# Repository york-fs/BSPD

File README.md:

# Brake System Plausibility Device

Uses non-programmable logic to implement the Brake System Plausibility Device required by FSUK rules. The BSPD opens the low-voltage shutdown circuit in the event of current being delivered to the motor while hard braking occurs.

## Features
- TODO

## PCB Notes
- Designed in KiCad 9.0

## Cloning

A recursive clone must be used to download the `kicad-library` repository:

    git clone --recursive https://github.com/york-fs/bspd.git

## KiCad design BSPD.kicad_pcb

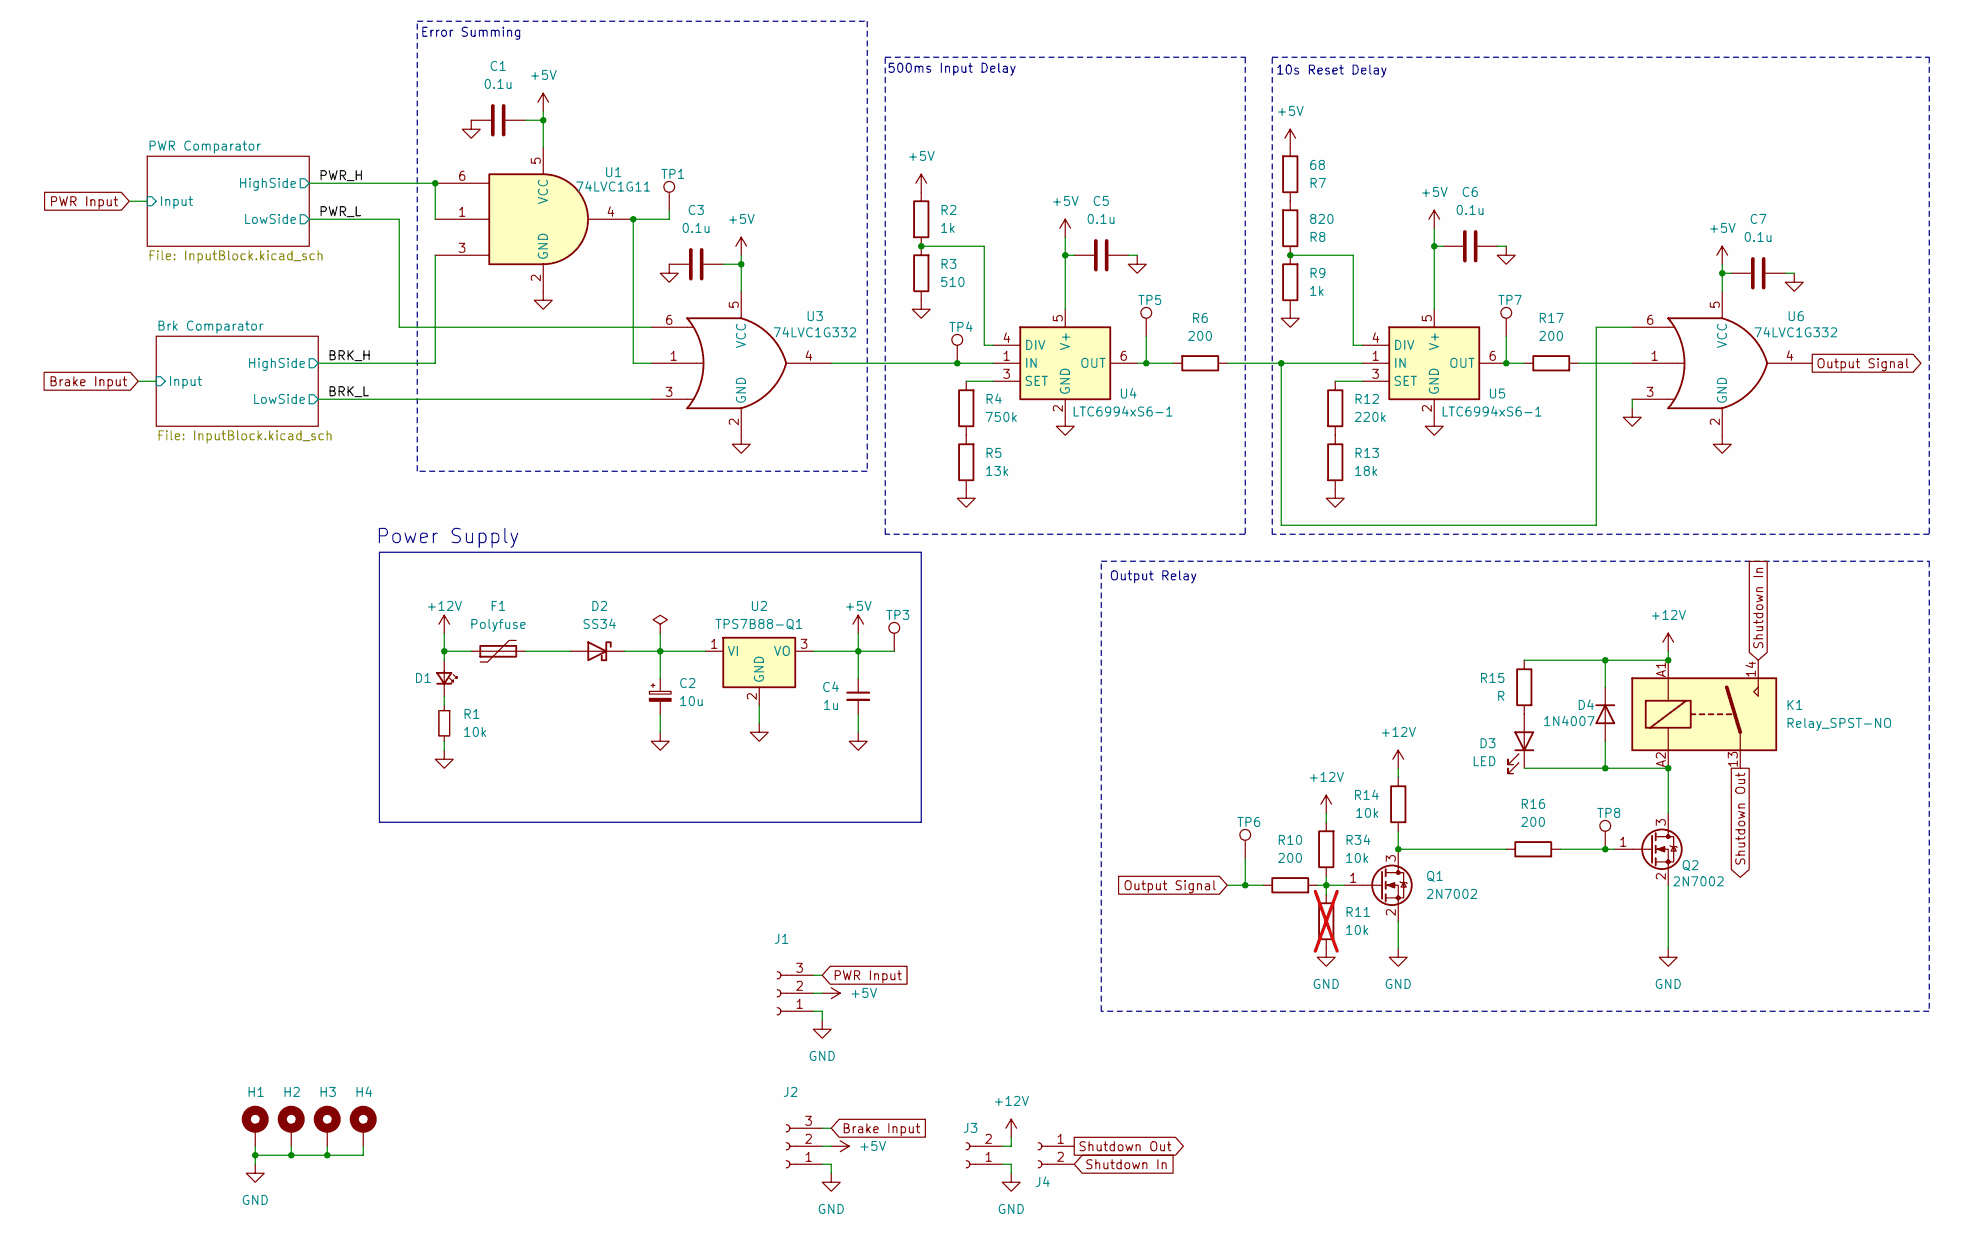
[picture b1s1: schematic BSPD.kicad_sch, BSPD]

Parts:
C1, C3, C5, C6, C7: 0.1u; C_0603_1608Metric
C2: 10u; CP_Elec_6.3x5.4
C4: 1u; C_0603_1608Metric
D1: LED_Small; LED_0603_1608Metric
D2: SS34; D_SMA
D3: LED; LED_0603_1608Metric
D4: 1N4007; D_SOD-123F
F1: Polyfuse; R_0805_2012Metric
H1, H2, H3, H4: MountingHole_Pad; MountingHole_3.2mm_M3_Pad_Via
J1, J2: Conn_01x03_Socket; MolexMicrofitPlus1x3
J3, J4: Conn_01x02_Socket; MolexMicrofitPlus1x2
K1: Relay_SPST-NO; Relay_SPST_Omron_G2RL-1A
Q1, Q2: 2N7002; SOT-23
R1, R14, R34: 10k; R_0603_1608Metric
R2, R9: 1k; R_0603_1608Metric
R3: 510; R_0603_1608Metric
R4: 750k; R_0603_1608Metric
R5: 13k; R_0603_1608Metric
R6, R10, R16, R17: 200; R_0603_1608Metric
R7: 68; R_0603_1608Metric
R8: 820; R_0603_1608Metric
R11: 10k; R_0603_1608Metric; not fitted
R12: 220k; R_0603_1608Metric
R13: 18k; R_0603_1608Metric
R15: R; R_0603_1608Metric
TP1, TP3, TP4, TP5, TP6, TP7, TP8: TestPoint; TestPoint_Keystone_5000-5004_Miniature
U1: 74LVC1G11; SOT-23-6
U2: TPS7B88-Q1; TO-252-2
U3, U6: 74LVC1G332; SOT-23-6
U4, U5: LTC6994xS6-1; TSOT-23-6

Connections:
+5V: C1.1, C3.1, C4.1, C5.2, C6.1, C7.1, J1.2, J2.2, R2.1, R7.2, TP3.1, U1.5 (VCC), U2.3 (VO), U3.5 (VCC), U4.5 (V+), U5.5 (V+), U6.5 (VCC); also elsewhere on the board
+12V: D1.2 (A), D4.1 (K), F1.1, J3.2, K1.A1, R14.1, R15.1, R34.2
/BRK_H: U1.3; also elsewhere on the board
/BRK_L: U3.3; also elsewhere on the board
/PWR_H: U1.1, U1.6; also elsewhere on the board
/PWR_L: U3.6; also elsewhere on the board
Brake Input: J2.3; also elsewhere on the board
GND: C1.2, C2.2, C3.2, C4.2, C5.1, C6.2, C7.2, H1.1, H2.1, H3.1, H4.1, J1.1, J2.1, J3.1, Q1.2 (S), Q2.2 (S), R1.2, R3.1, R5.1, R9.1, R11.2, R13.2, U1.2 (GND), U2.2 (GND), U3.2 (GND), U4.2 (GND), U5.2 (GND), U6.2 (GND), U6.3; also elsewhere on the board
unnamed: D1.1 (K), R1.1
unnamed: D2.2 (A), F1.2
unnamed: C2.1, D2.1 (K), U2.1 (VI)
unnamed: D3.2 (A), R15.2
unnamed: D3.1 (K), D4.2 (A), K1.A2, Q2.3 (D)
unnamed: Q1.3 (D), R14.2, R16.1
unnamed: Q1.1 (G), R10.2, R11.1, R34.1
unnamed: Q2.1 (G), R16.2, TP8.1
unnamed: R4.1, R5.2
unnamed: R7.1, R8.2
unnamed: R12.2, R13.1
unnamed: R17.2, U6.1
unnamed: TP1.1, U1.4, U3.1
unnamed: R2.2, R3.2, U4.4 (DIV)
unnamed: TP4.1, U3.4, U4.1 (IN)
unnamed: R6.2, TP5.1, U4.6 (OUT)
unnamed: R4.2, U4.3 (SET)
unnamed: R8.1, R9.2, U5.4 (DIV)
unnamed: R6.1, U5.1 (IN), U6.6
unnamed: R17.1, TP7.1, U5.6 (OUT)
unnamed: R12.1, U5.3 (SET)
Output Signal: R10.1, TP6.1, U6.4
PWR Input: J1.3; also elsewhere on the board
Shutdown In: J4.2, K1.14
Shutdown Out: J4.1, K1.13

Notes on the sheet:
500ms Input Delay
Error Summing
Power Supply
10s Reset Delay
Output Relay

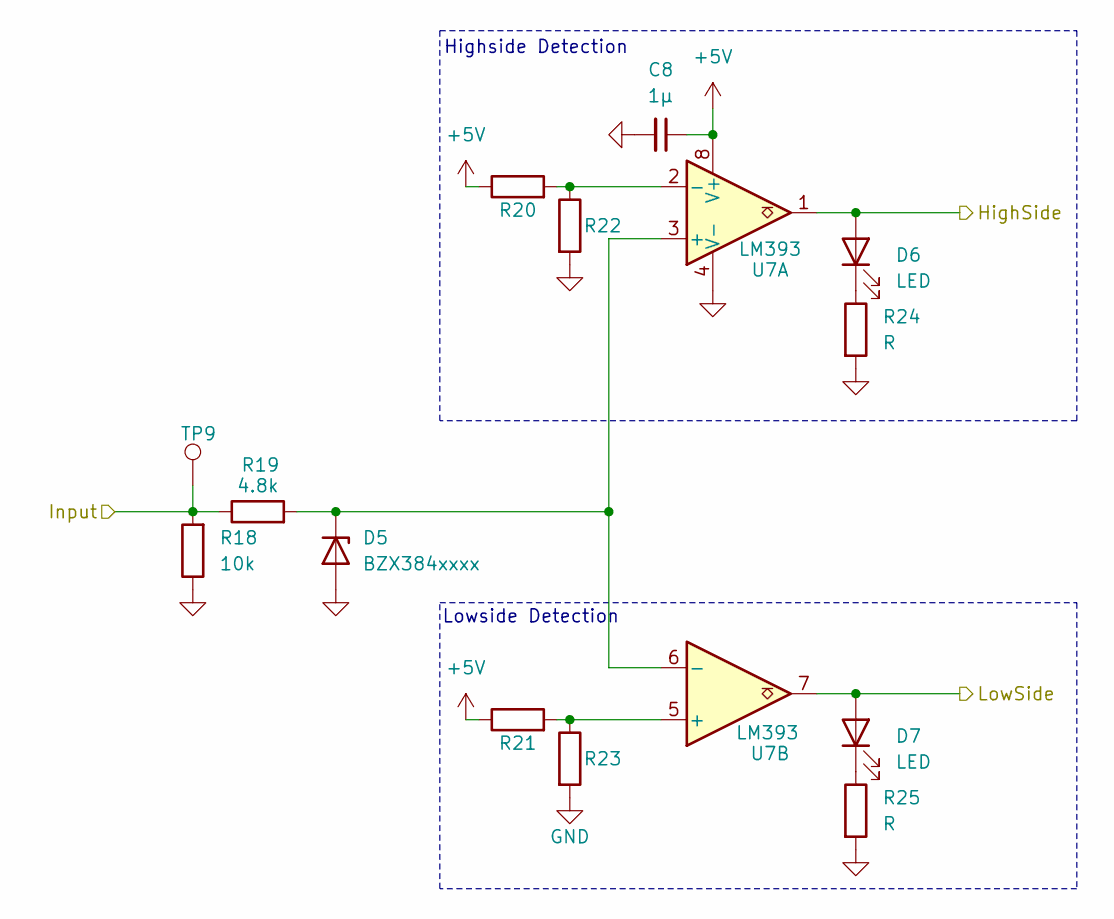
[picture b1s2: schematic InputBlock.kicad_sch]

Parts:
C8: 1µ; C_0603_1608Metric
D5: BZX384xxxx; D_SOD-323
D6, D7: LED; LED_0603_1608Metric
R18: 10k; R_0603_1608Metric
R19: 4.8k; R_0603_1608Metric
R20, R21: 39K; R_0603_1608Metric
R22, R23: 62k; R_0603_1608Metric
R24, R25: R; R_0603_1608Metric
TP9: TestPoint; TestPoint_Keystone_5000-5004_Miniature
U7: LM393; SOIC-8_3.9x4.9mm_P1.27mm

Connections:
+5V: C8.1, R20.1, R21.1, U7.8 (V+); also elsewhere on the board
/PWR_H: D6.2 (A), U7.1; also elsewhere on the board
/PWR_L: D7.2 (A), U7.7; also elsewhere on the board
GND: C8.2, D5.2 (A), R18.1, R22.2, R23.2, R24.2, R25.2, U7.4 (V-); also elsewhere on the board
unnamed: D5.1 (K), R19.2, U7.3 (+), U7.6 (-)
unnamed: D6.1 (K), R24.1
unnamed: D7.1 (K), R25.1
unnamed: R20.2, R22.1, U7.2 (-)
unnamed: R21.2, R23.1, U7.5 (+)
PWR Input: R18.2, R19.1, TP9.1; also elsewhere on the board

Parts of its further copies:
C9: 1µ; C_0603_1608Metric
D8: BZX384xxxx; D_SOD-323
D9, D10: LED; LED_0603_1608Metric
R26: 10k; R_0603_1608Metric
R27: 4.8k; R_0603_1608Metric
R28, R29: 39K; R_0603_1608Metric
R30, R31: 62k; R_0603_1608Metric
R32, R33: R; R_0603_1608Metric
TP10: TestPoint; TestPoint_Keystone_5000-5004_Miniature
U8: LM393; SOIC-8_3.9x4.9mm_P1.27mm

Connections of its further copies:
+5V: C9.1, R28.1, R29.1, U8.8 (V+); also elsewhere on the board
/BRK_H: D9.2 (A), U8.1; also elsewhere on the board
/BRK_L: D10.2 (A), U8.7; also elsewhere on the board
Brake Input: R26.2, R27.1, TP10.1; also elsewhere on the board
GND: C9.2, D8.2 (A), R26.1, R30.2, R31.2, R32.2, R33.2, U8.4 (V-); also elsewhere on the board
unnamed: D8.1 (K), R27.2, U8.3 (+), U8.6 (-)
unnamed: D9.1 (K), R32.1
unnamed: D10.1 (K), R33.1
unnamed: R28.2, R30.1, U8.2 (-)
unnamed: R29.2, R31.1, U8.5 (+)

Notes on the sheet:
Highside Detection
Lowside Detection

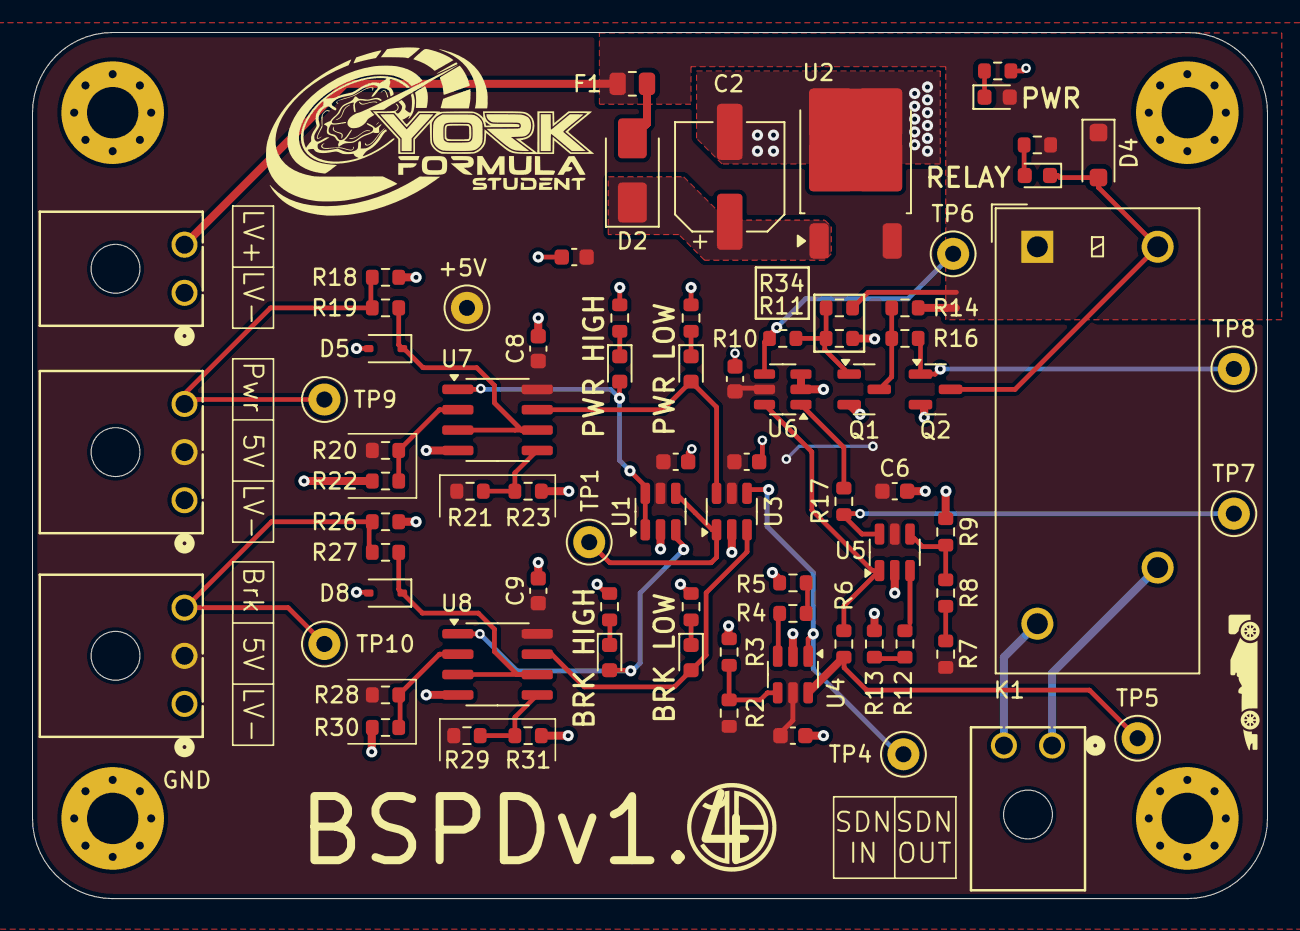
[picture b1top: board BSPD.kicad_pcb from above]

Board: 2 copper layers, 77.0 x 54.0 mm, 82 parts (0 on the bottom side), 43 nets.

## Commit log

2025-10-03 Initial commit v1.3
2025-10-05 Updated production gerbers
    Reversed shutdown connector
    Added back test points 1 and 2
    Fixed shutdown connector placement
2025-10-23 V1.4
    Replaced Comparators for push pull (not yet selected)
    Changed input block to 5V
    Added more test points
    Changed Zener Package
    Moved Diodes to active high
2025-10-23 Cleaned up repo
2025-10-23 Linked footprint library
2025-10-23 Rename gitmodules.txt to .gitmodules
2025-10-25 kicad-library: Update to latest version
2025-10-25 Updated connector colours
2025-10-25 project: Add footprint library
2025-10-25 Updated footprints
2025-11-22 meta: Update gitignore
2025-11-22 meta: Set LF line endings explicitly
2025-11-23 ci: Add kicad workflow
2025-11-23 meta: Add some badges to the README
